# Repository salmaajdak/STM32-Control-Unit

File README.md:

# STM32-Based Control Unit
## Project Overview

This engineering project was developed at ENSEA (École Nationale Supérieure de l'Électronique et de ses Applications) as part of a team-based electronics project.

The objective was to design a control unit based on an STM32 microcontroller for a power converter, combining embedded electronics, a human-machine interface, and custom printed circuit boards (PCBs).

The system includes an STM32L476RG microcontroller, a TFT display, push buttons, a rotary encoder, and dedicated electronic boards.

## My Contributions

As a member of the project team, I was responsible for the PCB design work on two boards:

- Button interface PCB: electronic schematic, component placement, and PCB routing.
- USB-C communication PCB: electronic schematic, component placement, and PCB routing.

The broader project involved STM32 programming and hardware/software integration, carried out collaboratively by the team.

## Hardware Design

### 1. Button Interface PCB

A custom PCB designed with KiCad for the control unit's push-button interface and user controls.

### 2. USB-C Communication PCB

A dedicated PCB designed with KiCad to support the control unit's USB-C interface and associated electronic connections.

## Technologies and Tools

- KiCad — schematic capture and PCB layout
- STM32L476RG — ARM Cortex-M4 microcontroller
- Embedded electronics and circuit design
- USB-C interface
- Human-machine interface (HMI)

## Project Files

- [Button Interface PCB](hardware/button-interface/)
- [USB-C Communication PCB](hardware/usb-c-communication/)

## Project Context

Institution: ENSEA, France

Project type: Team-based engineering project

Focus: Embedded systems, electronic design, and PCB development

## Project Gallery

### STM32 Control Unit

### Complete Motor Control System

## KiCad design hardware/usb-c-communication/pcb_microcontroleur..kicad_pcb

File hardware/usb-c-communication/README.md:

# USB-C Communication PCB

PCB designed with KiCad for the control unit's USB-C communication interface.

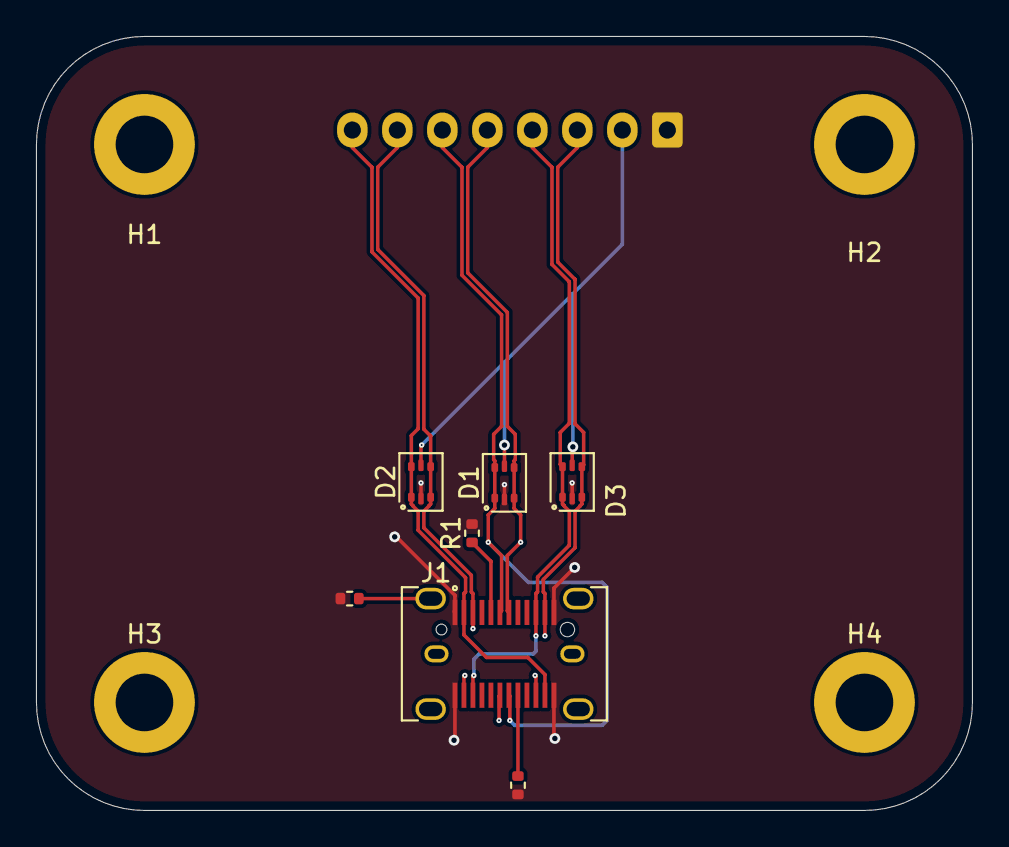
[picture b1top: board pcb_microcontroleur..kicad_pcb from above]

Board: 4 copper layers, 52.0 x 43.0 mm, 12 parts (1 on the bottom side), 11 nets.

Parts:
D1, D2, D3: USBLC6-2P6; SOT-666
H1, H2, H3, H4: MountingHole; MountingHole_3.2mm_M3_DIN965_Pad
J1: USB_C_Receptacle; USB_C_Receptacle_JAE_DX07S024WJ1R350
J2: Conn_01x08; JST_EH_B8B-EH-A_1x08_P2.50mm_Vertical
R1, R2: 5.1k; R_0402_1005Metric
R3: 0; R_0402_1005Metric

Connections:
+3,3V: D1.5 (VP), D2.5 (VP), D3.5 (VP), J2.2
GND: D1.2 (VN), D2.2 (VN), D3.2 (VN), J1.A1 (GND), J1.A12 (GND), J1.B1 (GND), J1.B12 (GND), J2.1, R1.2, R2.2, R3.1
unnamed: J1.A5 (CC1), R1.1
unnamed: J1.B5 (CC2), R2.1
unnamed: J1.S1 (SHIELD), R3.2
RX_N: D3.1 (L1), D3.6 (L1), J1.A10 (RX2-), J1.B10 (RX1-), J2.4
RX_P: D3.3 (L2), D3.4 (L2), J1.A11 (RX2+), J1.B11 (RX1+), J2.3
TX_N: D2.1 (L1), D2.6 (L1), J1.A2 (TX1+), J1.B2 (TX2+), J2.8
TX_P: D2.3 (L2), D2.4 (L2), J1.A3 (TX1-), J1.B3 (TX2-), J2.7
USB_D_N: D1.3 (L2), D1.4 (L2), J1.A7 (D-), J1.B7 (D-), J2.5
USB_D_P: D1.1 (L1), D1.6 (L1), J1.A6 (D+), J1.B6 (D+), J2.6

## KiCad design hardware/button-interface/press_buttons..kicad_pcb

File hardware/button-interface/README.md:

# Button Interface PCB

PCB designed with KiCad for the control unit's push-button interface.

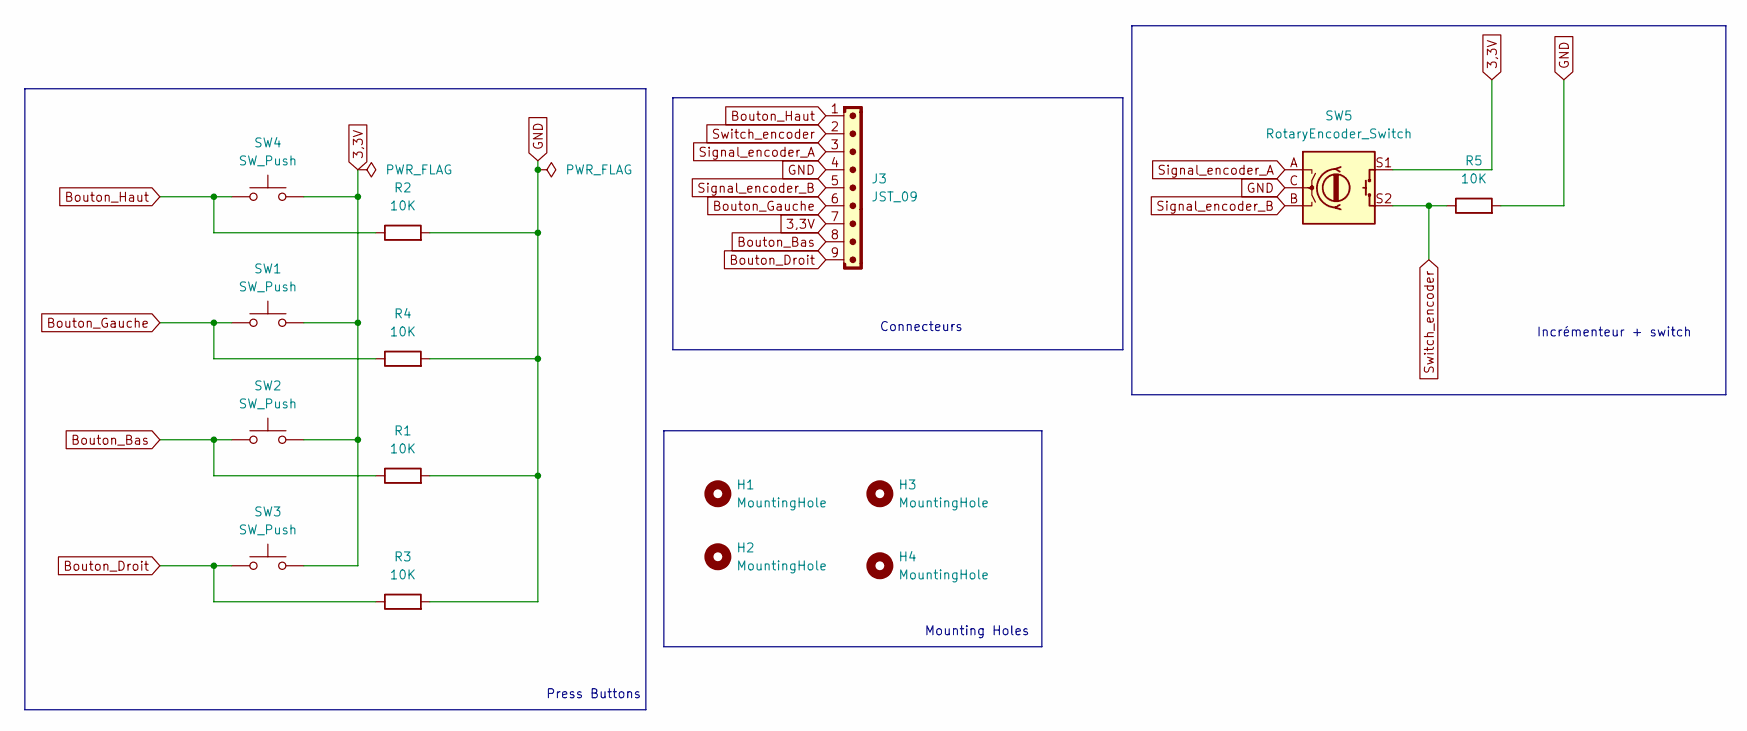
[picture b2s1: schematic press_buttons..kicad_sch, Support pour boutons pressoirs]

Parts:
H1, H2, H3, H4: MountingHole; MountingHole_3.2mm_M3_DIN965_Pad
J3: JST_09; JST_EH_B9B-EH-A_1x09_P2.50mm_Vertical
R1, R2, R3, R4, R5: 10K; R_0603_1608Metric_Pad0.98x0.95mm_HandSolder
SW1, SW2, SW3, SW4: SW_Push; SW_PUSH_6mm
SW5: RotaryEncoder_Switch; RotaryEncoder_Alps_EC11E-Switch_Vertical_H20mm

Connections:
3,3V: J3.7, SW1.2, SW2.2, SW3.2, SW4.2, SW5.S1
Bouton_Bas: J3.8, R1.1, SW2.1
Bouton_Droit: J3.9, R3.1, SW3.1
Bouton_Gauche: J3.6, R4.1, SW1.1
Bouton_Haut: J3.1, R2.1, SW4.1
GND: J3.4, R1.2, R2.2, R3.2, R4.2, R5.2, SW5.C
Signal_encoder_A: J3.3, SW5.A
Signal_encoder_B: J3.5, SW5.B
Switch_encoder: J3.2, R5.1, SW5.S2

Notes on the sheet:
Incrémenteur + switch
Mounting Holes
Connecteurs
Press Buttons

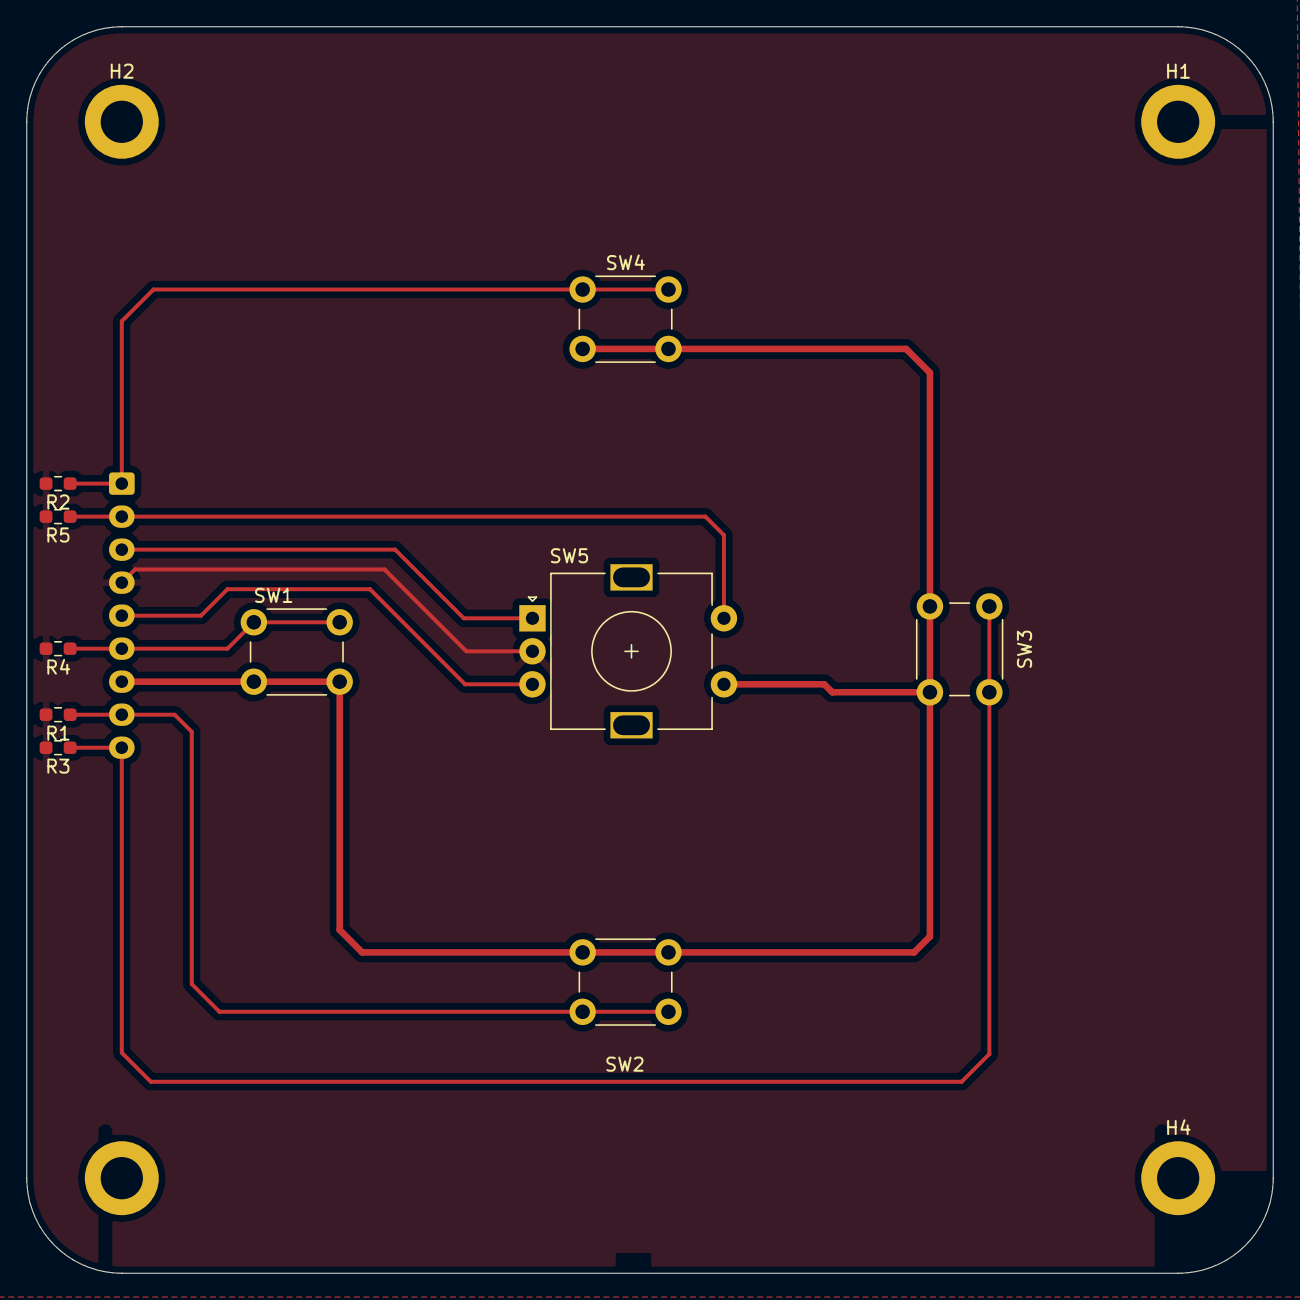
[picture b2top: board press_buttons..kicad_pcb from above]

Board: 2 copper layers, 94.4 x 94.4 mm, 15 parts (1 on the bottom side), 9 nets.
